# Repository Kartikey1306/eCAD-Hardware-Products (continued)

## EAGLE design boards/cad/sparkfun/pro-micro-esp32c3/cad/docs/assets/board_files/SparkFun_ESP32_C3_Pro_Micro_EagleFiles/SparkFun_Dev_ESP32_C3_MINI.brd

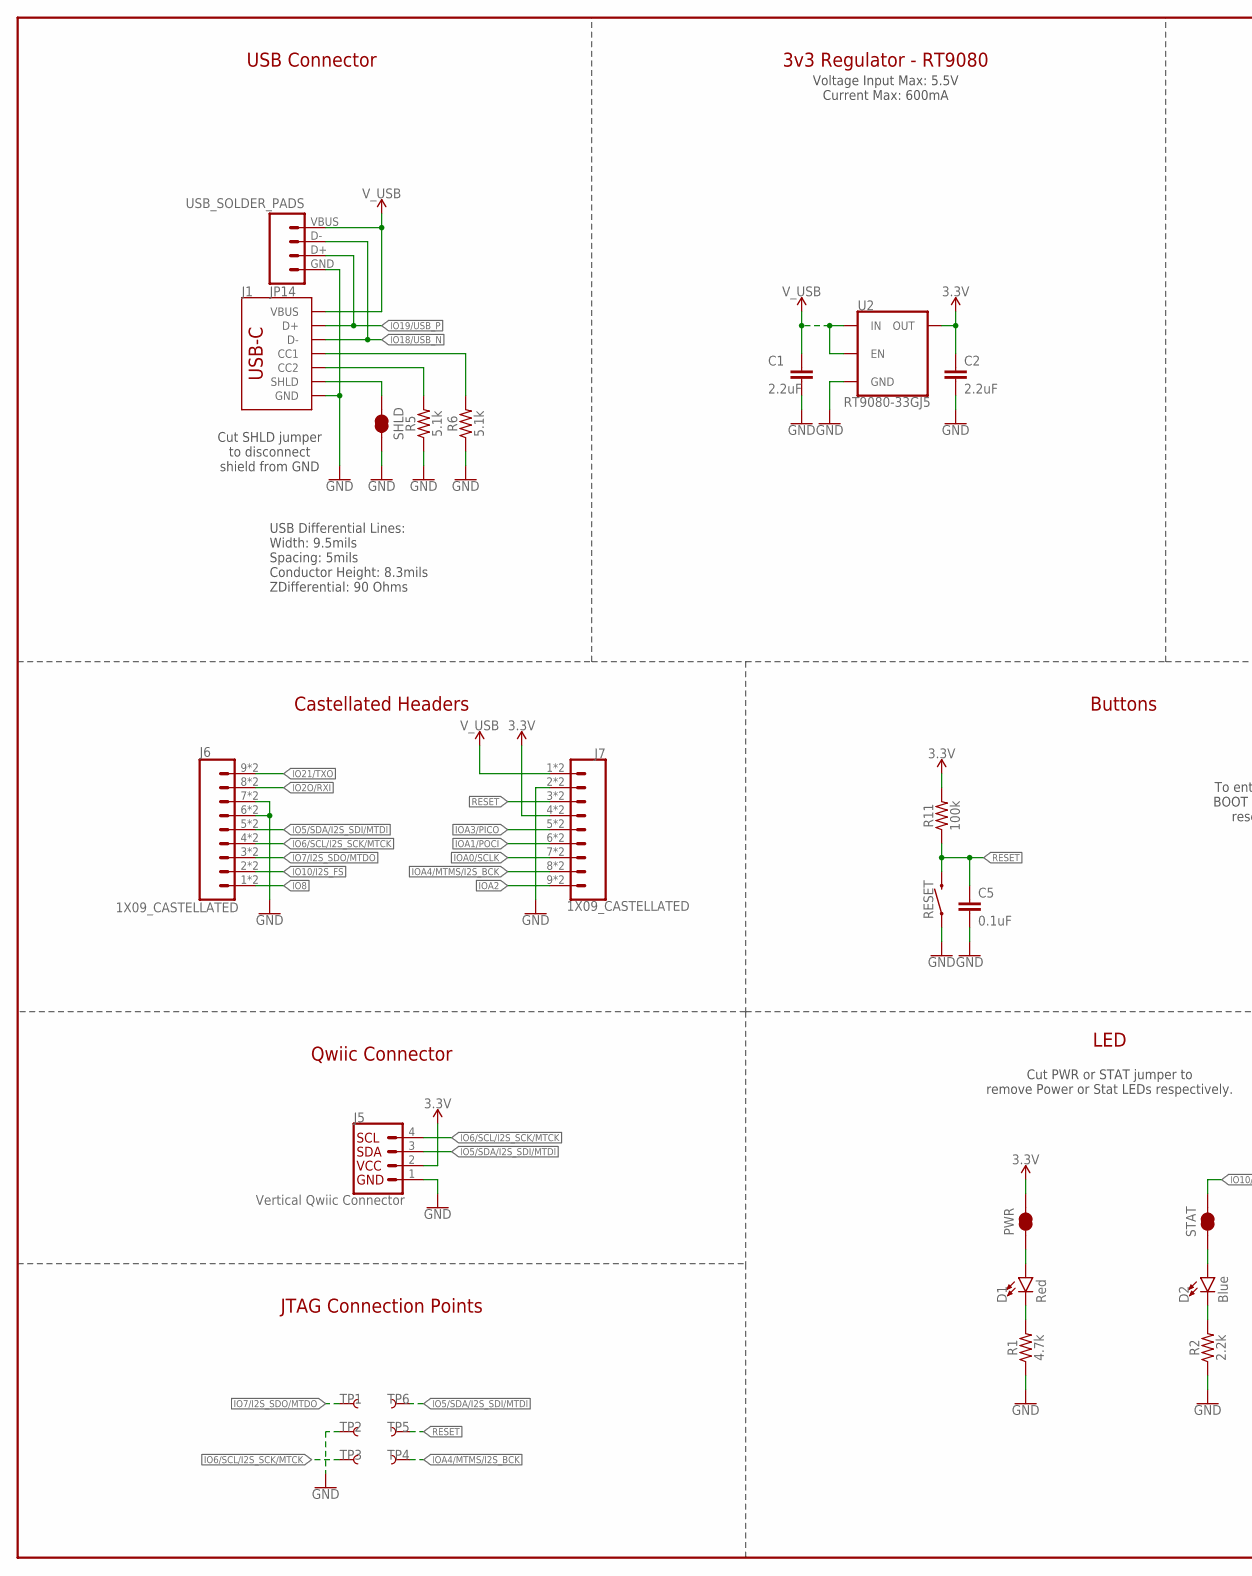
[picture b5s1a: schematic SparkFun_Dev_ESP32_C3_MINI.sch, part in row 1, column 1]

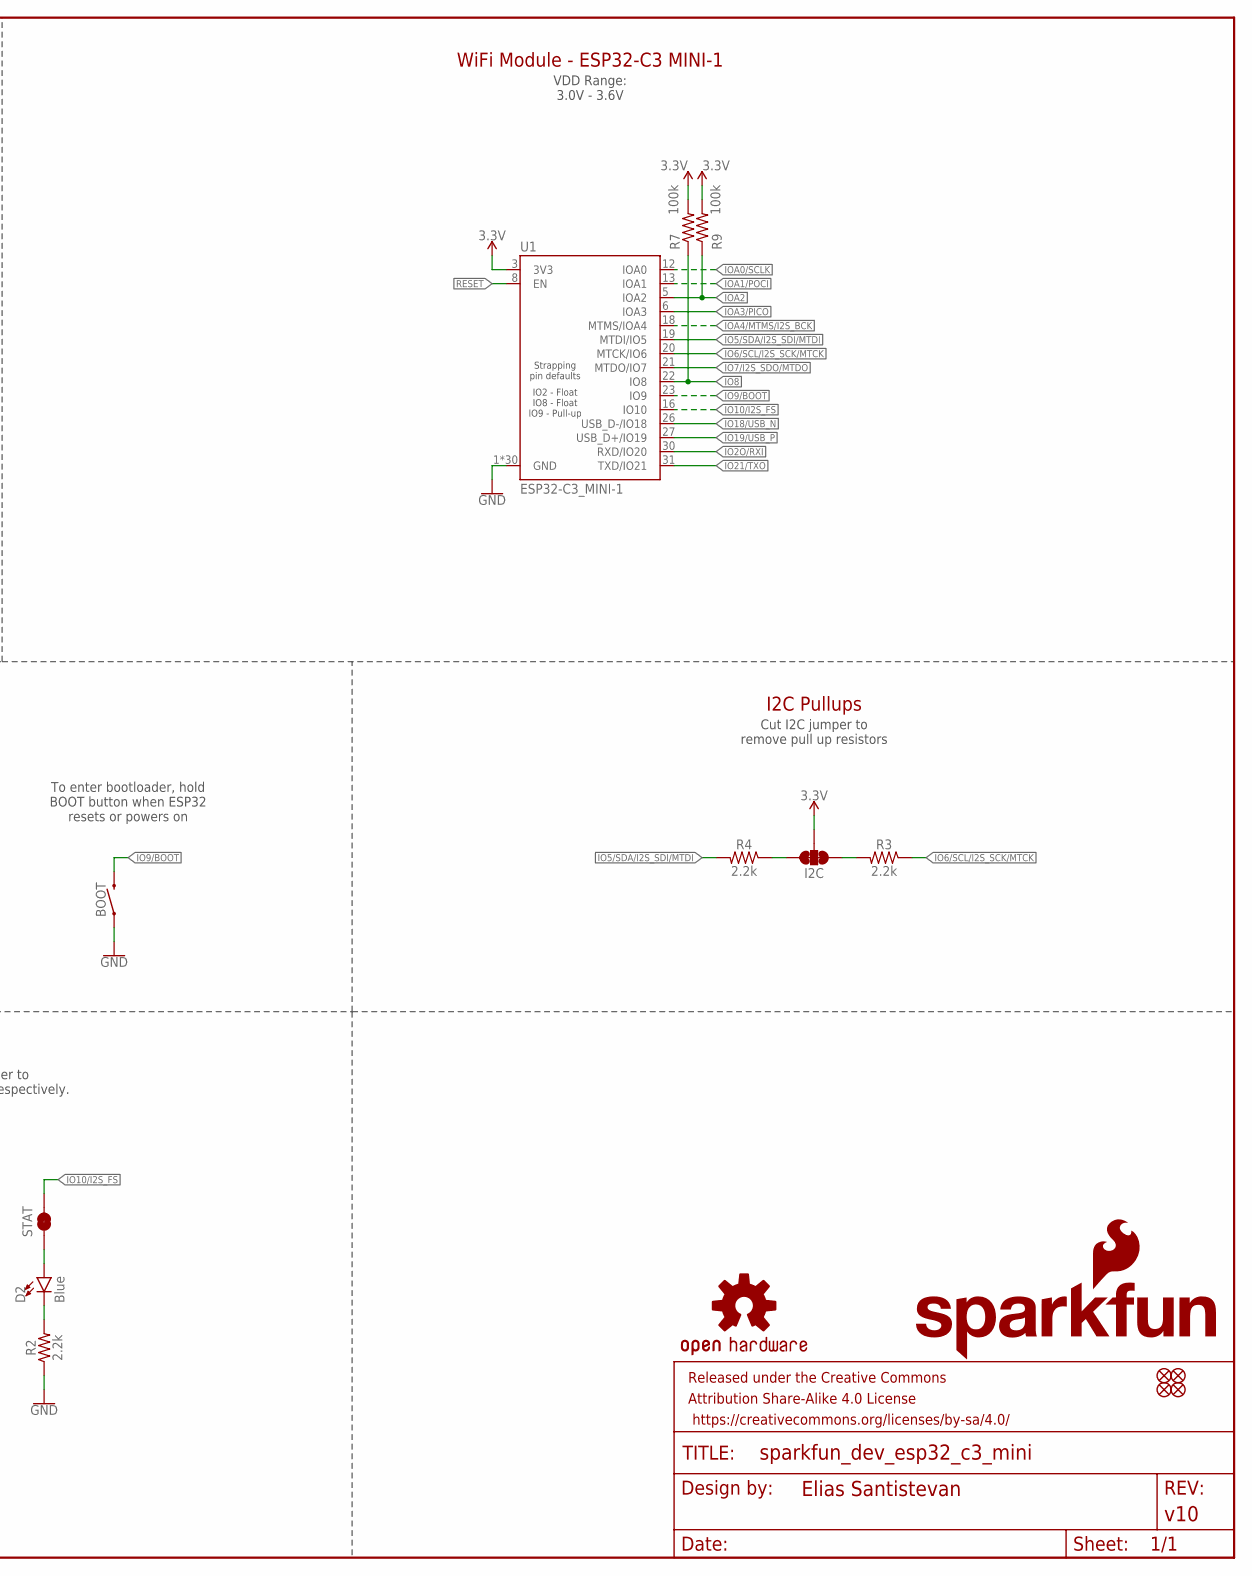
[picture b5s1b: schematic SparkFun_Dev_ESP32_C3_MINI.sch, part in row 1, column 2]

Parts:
BOOT: MOMENTARY-SWITCH-SPST-SMD-4.6X2.8MM; TACTILE_SWITCH_SMD_4.6X2.8MM
C1, C2: 2.2uF; 0402-TIGHT
C5: 0.1uF; 0402-TIGHT
D1: Red; LED-0603
D2: Blue; LED-0603
FD1, FD2, FD3, FD4: FIDUCIALUFIDUCIAL; FIDUCIAL-MICRO
FRAME2: FRAME-LEDGER; CREATIVE_COMMONS
I2C: JUMPER-SMT_3_2-NC_TRACE_SILK; SMT-JUMPER_3_2-NC_TRACE_SILK
J1: USB Female Type C Connector; USB-C-16P_4LAYER-PADS
J5: Vertical Qwiic Connector; JST04_1MM_VERT
J6, J7: 1X09_CASTELLATED
JP14: USB_SOLDER_PADS; USB-SOLDER-PADS
LOGO1: SFE_LOGO_NAME_FLAMEBLANK; BLANK
LOGO3: OSHW-LOGOS; OSHW-LOGO-S
PWR: JUMPER-SMT_2_NC_TRACE_SILK; SMT-JUMPER_2_NC_TRACE_SILK
R1: 4.7k; 0402-TIGHT
R2, R3, R4: 2.2k; 0402-TIGHT
R5, R6: 5.1k; 0402-TIGHT
R7, R9, R11: 100k; 0402-TIGHT
RESET: MOMENTARY-SWITCH-SPST-SMD-4.6X2.8MM; TACTILE_SWITCH_SMD_4.6X2.8MM
SHLD: JUMPER-SMT_2_NC_TRACE_SILK; SMT-JUMPER_2_NC_TRACE_SILK
STAT: JUMPER-SMT_2_NC_TRACE_SILK; SMT-JUMPER_2_NC_TRACE_SILK
TP1, TP2, TP3, TP4, TP5, TP6: TEST-POINT3X5; PAD.03X.05
U1: ESP32-C3_MINI-1; ESP32-C3-MINI-1
U2: RT9080-33GJ5; SOT23-5

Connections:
3.3V: C2.1, I2C.2, J5.2, J7.4, J7.4B (4), PWR.2, R7.2, R9.2, R11.2, U1.3 (3V3), U2.5 (OUT)
!RESET!: C5.1, J7.3, J7.3B (3), R11.1, RESET.3 (2), RESET.4 (2), TP5.1, U1.8 (EN)
GND: BOOT.1, BOOT.2 (1), C1.2, C2.2, C5.2, J1.GND, J1.GND2 (GND), J5.1, J6.6, J6.6B (6), J6.7, J6.7B (7), J7.2, J7.2B (2), JP14.GND (4), R1.1, R2.1, R5.1, R6.1, RESET.1, RESET.2 (1), SHLD.2, TP2.1, U1.1 (GND), U1.2 (GND), U1.11 (GND), U1.14 (GND), U1.36 (GND), U1.37 (GND), U1.38 (GND), U1.39 (GND), U1.40 (GND), U1.41 (GND), U1.42 (GND), U1.43 (GND), U1.44 (GND), U1.45 (GND), U1.46 (GND), U1.47 (GND), U1.48 (GND), U1.49.1 (GND), U1.49.2 (GND), U1.49.3 (GND), U1.49.4 (GND), U1.49.5 (GND), U1.49.6 (GND), U1.49.7 (GND), U1.49.8 (GND), U1.49.9 (GND), U1.50 (GND), U1.51 (GND), U1.52 (GND), U1.53 (GND), U2.2 (GND)
IO2O/RXI: J6.8, J6.8B (8), U1.30 (RXD/IO20)
IO5/SDA/I2S_SDI/MTDI: J5.3, J6.5, J6.5B (5), R4.2, TP6.1, U1.19 (MTDI/IO5)
IO6/SCL/I2S_SCK/MTCK: J5.4, J6.4, J6.4B (4), R3.1, TP3.1, U1.20 (MTCK/IO6)
IO7/I2S_SDO/MTDO: J6.3, J6.3B (3), TP1.1, U1.21 (MTDO/IO7)
IO8: J6.1, J6.1B (1), R7.1, U1.22 (IO8)
IO9/BOOT: BOOT.3 (2), BOOT.4 (2), U1.23 (IO9)
IO10/I2S_FS: J6.2, J6.2B (2), STAT.2, U1.16 (IO10)
IO18/USB_N: J1.A7 (D-), J1.B7 (D-), JP14.D- (2), U1.26 (USB_D-/IO18)
IO19/USB_P: J1.A6 (D+), J1.B6 (D+), JP14.D+ (3), U1.27 (USB_D+/IO19)
IO21/TXO: J6.9, J6.9B (9), U1.31 (TXD/IO21)
IOA0/SCLK: J7.7, J7.7B (7), U1.12 (IOA0)
IOA1/POCI: J7.6, J7.6B (6), U1.13 (IOA1)
IOA2: J7.9, J7.9B (9), R9.1, U1.5 (IOA2)
IOA3/PICO: J7.5, J7.5B (5), U1.6 (IOA3)
IOA4/MTMS/I2S_BCK: J7.8, J7.8B (8), TP4.1, U1.18 (MTMS/IOA4)
unnamed: D1.C, R1.2
unnamed: D1.A, PWR.1
unnamed: D2.C, R2.2
unnamed: I2C.3, R3.2
unnamed: I2C.1, R4.1
unnamed: J1.B5 (CC2), R5.2
unnamed: J1.A5 (CC1), R6.2
unnamed: D2.A, STAT.1
SHLD: J1.SHLD1 (SHLD), J1.SHLD2 (SHLD), J1.SHLD3 (SHLD), J1.SHLD4 (SHLD), SHLD.1
V_USB: C1.1, J1.VBUS1 (VBUS), J1.VBUS2 (VBUS), J7.1, J7.1B (1), JP14.VBUS (1), U2.1 (IN), U2.3 (EN)

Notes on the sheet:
USB Connector
3v3 Regulator - RT9080
Qwiic Connector
Castellated Headers
LED
Buttons
I2C Pullups
WiFi Module - ESP32-C3 MINI-1
VDD Range: 3.0V - 3.6V
Cut I2C jumper to remove pull up resistors
Cut PWR or STAT jumper to remove Power or Stat LEDs respectively.
Voltage Input Max: 5.5V Current Max: 600mA
To enter bootloader, hold BOOT button when ESP32 resets or powers on
Cut SHLD jumper to disconnect shield from GND
JTAG Connection Points
USB Differential Lines: Width: 9.5mils Spacing: 5mils Conductor Height: 8.3mils ZDifferential: 90 Ohms

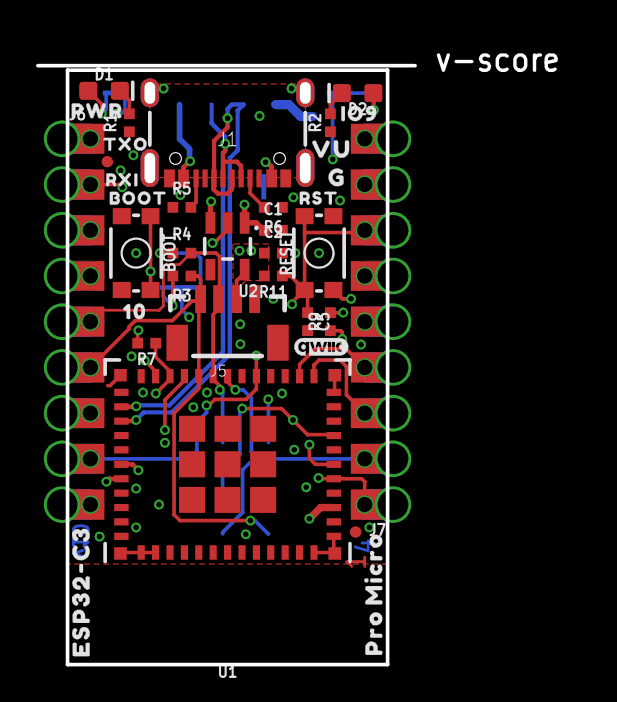
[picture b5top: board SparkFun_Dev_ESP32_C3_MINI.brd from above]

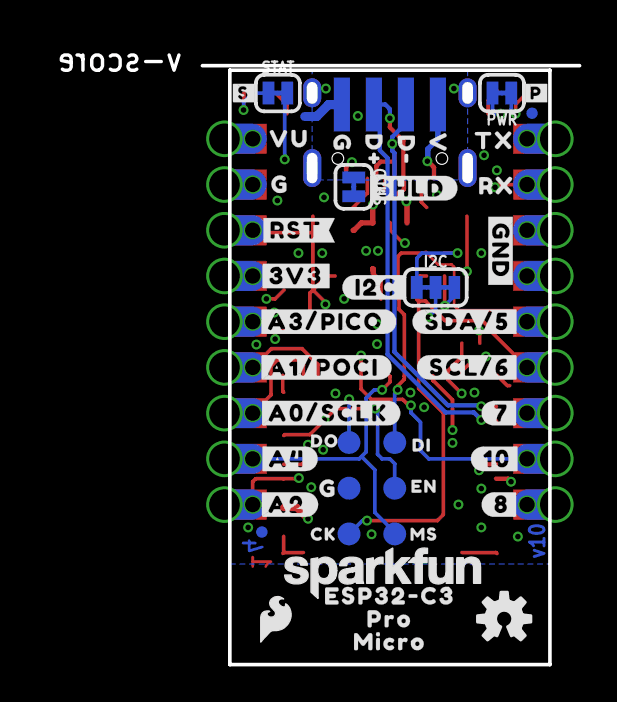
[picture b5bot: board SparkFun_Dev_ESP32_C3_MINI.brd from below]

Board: 4 copper layers, 17.8 x 33.0 mm, 90 parts (50 on the bottom side), 28 nets.

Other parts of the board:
U$1, U$31, U$33, U$39: G36
U$4: #3V3#0
U$5: RST41
U$6: #I2C#947
U$7: #P#49
U$8: #S#51
U$9: #RST#945
U$10, U$51: VU35
U$11: #SHLD#946
U$12: #8#50
U$13: #A1#POCI#50
U$14: #A0#SCLK#50
U$15: #A4#50
U$16: #A2#50
U$17: TX40
U$18: SFE_LOGO_NAME_.1
U$20: #7#50
U$21: #10#50
U$22: #GND#4
U$23: CK39
U$24: ORDERING_INSTRUCTIONS
U$25: D#33
U$26: D#34
U$27: DI36
U$28: DO35
U$29: EN37
U$30: MS38
U$32: V35
U$34, U$45: ESP32#C32
U$35, U$46: PRO0
U$36, U$47: MICRO1
U$37: RX39
U$38: 10950
U$40: #A3#PICO#45
U$41: BOOT15
U$42: RXI39
U$43: TXO40
U$44: #SDA#5#10952
U$48: SFE_LOGO_FLAME_.1
U$49: PWR945
U$50: QWIIC_3MM
U$52: IO944
U$53: #SCL#6#10952

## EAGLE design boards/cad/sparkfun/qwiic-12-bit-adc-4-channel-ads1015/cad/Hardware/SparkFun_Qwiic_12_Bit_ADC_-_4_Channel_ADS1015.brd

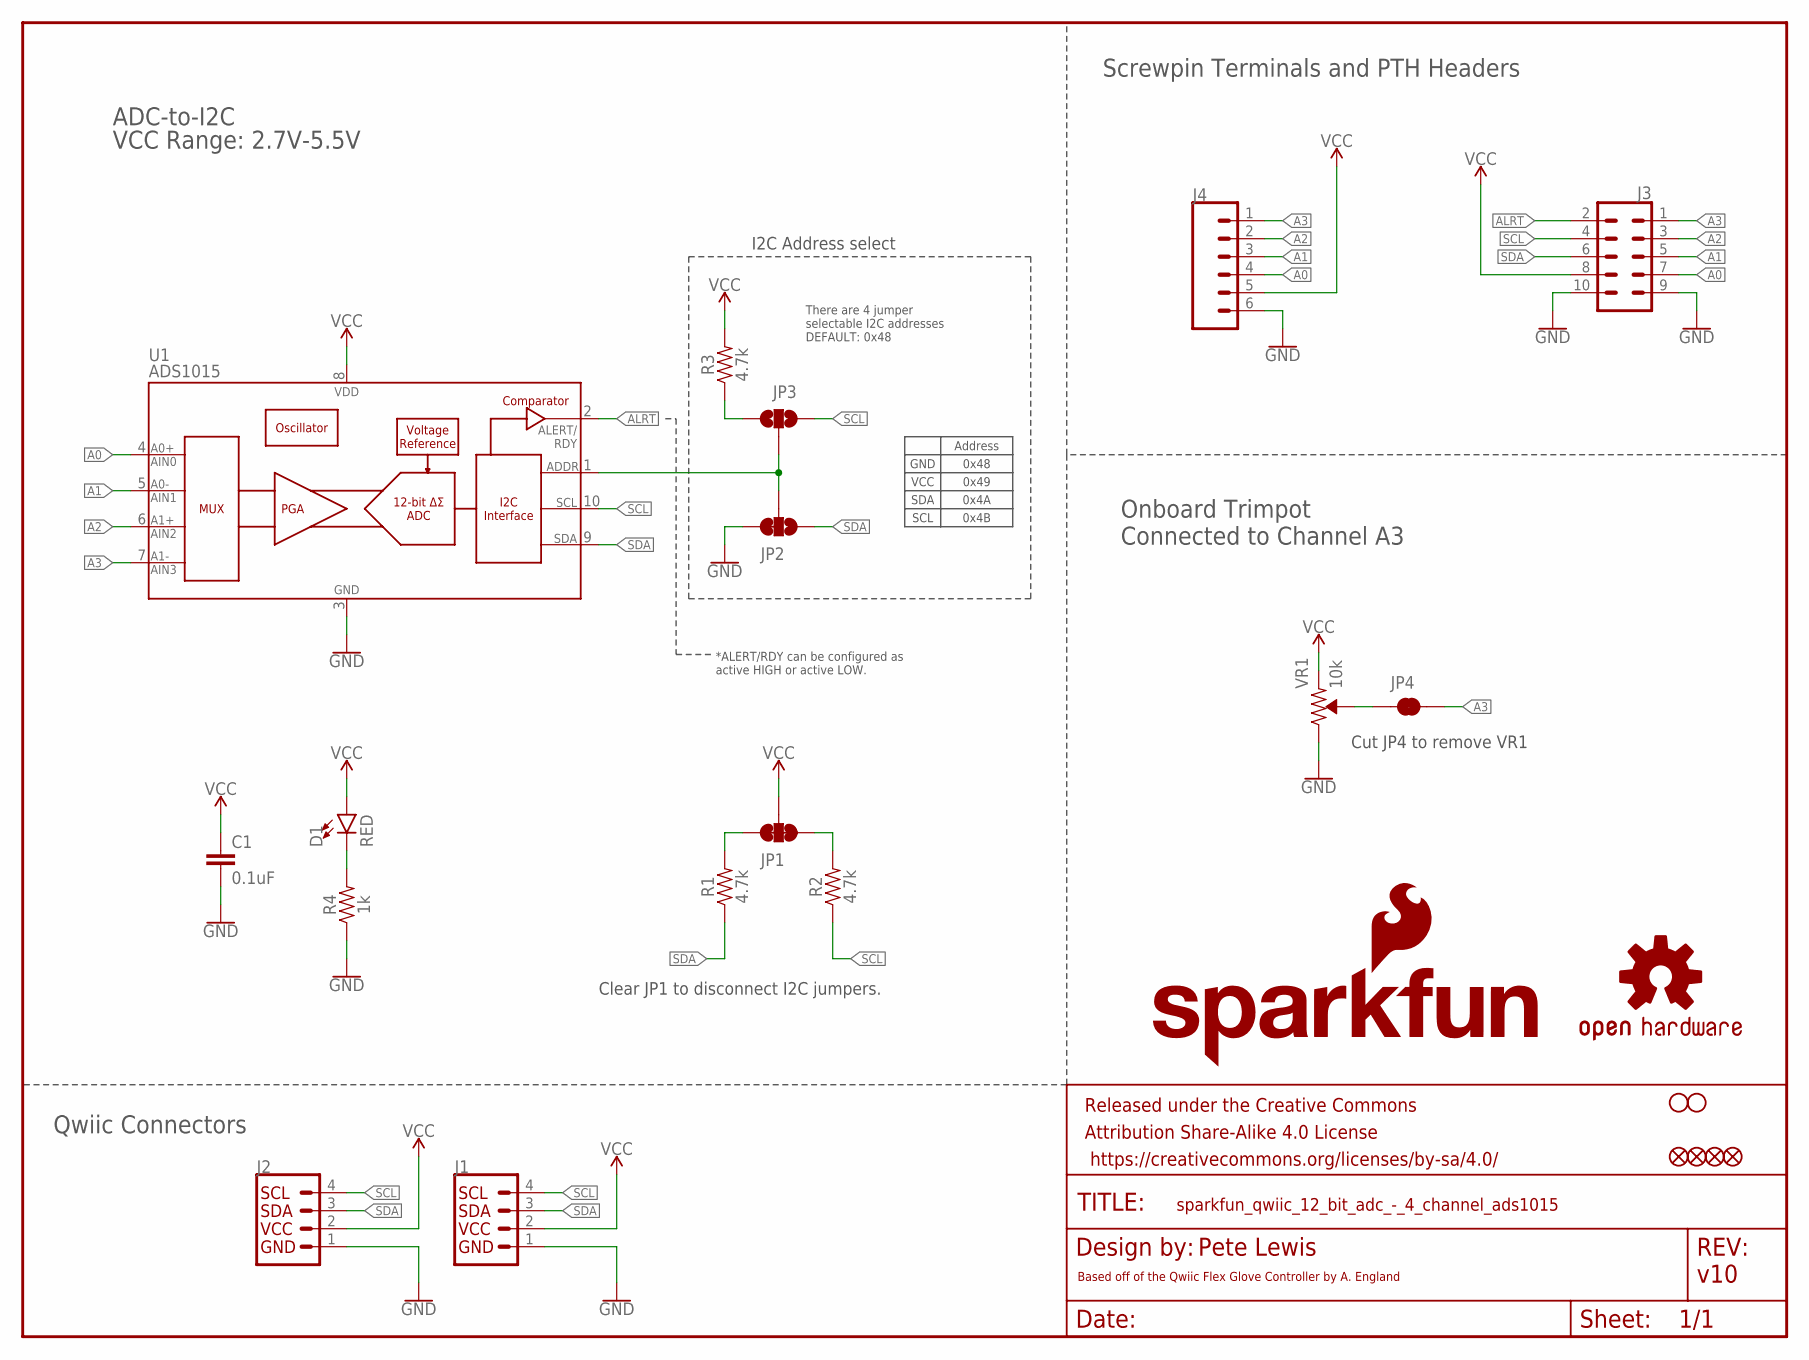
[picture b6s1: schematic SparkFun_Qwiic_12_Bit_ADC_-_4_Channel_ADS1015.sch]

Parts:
C1: 0.1uF; 0603
D1: RED; LED-0603
FD1, FD2, FD3, FD4: FIDUCIALUFIDUCIAL; FIDUCIAL-MICRO
FRAME1: FRAME-LETTER; CREATIVE_COMMONS
H1, H2: STAND-OFF
J1, J2: QWIIC_CONNECTORJS-1MM; JST04_1MM_RA
J3: CONN_05X2NO_SILK; 2X5_NOSILK
J4: Screw Pin; SCREWTERMINAL-3.5MM-6
JP1: JUMPER-SMT_3_2-NC_TRACE_NO-SILK; SMT-JUMPER_3_2-NC_TRACE_NO-SILK
JP2: JUMPER-SMT_3_1-NC_TRACE_NO-SILK; SMT-JUMPER_3_1-NC_TRACE_NO-SILK
JP3: JUMPER-SMT_3_NO_NO_SILK; SMT-JUMPER_3_0-NO_TRACE_NO-SILK
JP4: JUMPER-SMT_2_NC_TRACE_SILK; SMT-JUMPER_2_NC_TRACE_SILK
LOGO1: SFE_LOGO_NAME.1_INCH; SFE_LOGO_NAME_.1
LOGO2: OSHW-LOGOS; OSHW-LOGO-S
LOGO3: SFE_LOGO_FLAME.1_INCH; SFE_LOGO_FLAME_.1
R1, R2, R3: 4.7k; 0603
R4: 1k; 0603
U1: ADS1015; MSOP10
VR1: 10k; TRIMPOT-SMD-3MM-CLOSED

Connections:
A0: J3.7, J4.4, U1.4 (AIN0)
A1: J3.5, J4.3, U1.5 (AIN1)
A2: J3.3, J4.2, U1.6 (AIN2)
A3: J3.1, J4.1, JP4.2, U1.7 (AIN3)
ADDR: JP2.2, JP3.2, U1.1 (ADDR)
ALRT: J3.2, U1.2 (ALERT/RDY)
GND: C1.2, J1.1, J2.1, J3.9, J3.10, J4.6, JP2.3, R4.1, U1.3 (VSS), VR1.3 (CW)
unnamed: JP4.1, VR1.2 (WIPER)
unnamed: D1.C, R4.2
unnamed: JP3.1, R3.1
unnamed: JP1.1, R2.2
unnamed: JP1.3, R1.2
SCL: J1.4, J2.4, J3.4, JP3.3, R2.1, U1.10 (SCL)
SDA: J1.3, J2.3, J3.6, JP2.1, R1.1, U1.9 (SDA)
VCC: C1.1, D1.A, J1.2, J2.2, J3.8, J4.5, JP1.2, R3.2, U1.8 (VDD), VR1.1 (CCW)

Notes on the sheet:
v10
Qwiic Connectors
ADC-to-I2C
Pete Lewis
There are 4 jumper selectable I2C addresses DEFAULT: 0x48
Address
0x48
0x49
0x4A
0x4B
GND
VCC
SDA
SCL
VCC Range: 2.7V-5.5V
Clear JP1 to disconnect I2C jumpers.
Based off of the Qwiic Flex Glove Controller by A. England
Onboard Trimpot Connected to Channel A3
Cut JP4 to remove VR1
I2C Address select
Screwpin Terminals and PTH Headers
*ALERT/RDY can be configured as active HIGH or active LOW.

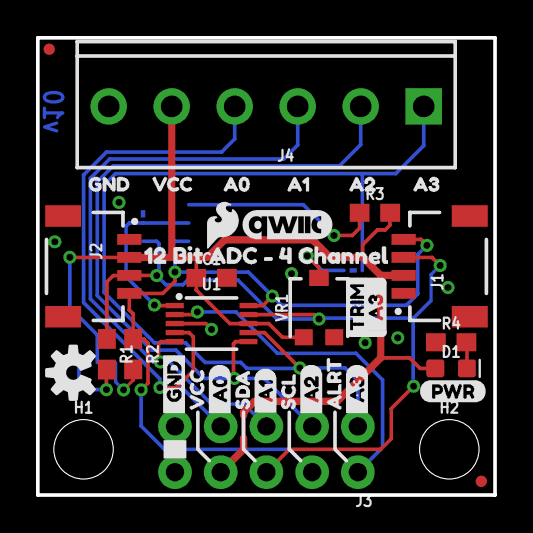
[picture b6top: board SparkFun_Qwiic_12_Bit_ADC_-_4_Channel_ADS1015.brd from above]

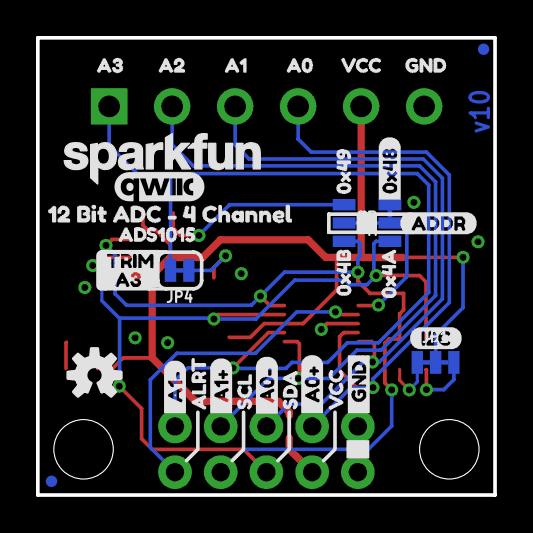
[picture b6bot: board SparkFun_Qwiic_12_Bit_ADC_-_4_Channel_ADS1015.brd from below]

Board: 2 copper layers, 25.4 x 25.4 mm, 73 parts (34 on the bottom side), 15 nets.

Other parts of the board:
U$1, U$18, U$30, U$34: VCC1
U$2, U$35: GND0
U$3: 0X4A2
U$4: 0X491
U$5, U$36: A02
U$6, U$37: A13
U$7, U$38: A24
U$8, U$39: A35
U$9: _A0#3
U$10: _A0#4
U$11, U$19: TRIM7
U$12: 0X4B3
U$13: OSHW-LOGO-S
U$14: _A1#5
U$15: _A1#6
U$16, U$43: 12_BIT_ADC_#_4_CHANNEL1
U$17, U$22: _A3_0
U$20, U$29: _GND17
U$21, U$31: SDA6
U$23, U$32: SCL7
U$24, U$33: ALRT8
U$25: _A013
U$26: _A114
U$27: _A215
U$28: _A316
U$40: PWR0
U$41: I2C1
U$42: 0X480
U$44, U$47: QWIIC_5MM
U$45: ADDR0
U$46: ADS10150
